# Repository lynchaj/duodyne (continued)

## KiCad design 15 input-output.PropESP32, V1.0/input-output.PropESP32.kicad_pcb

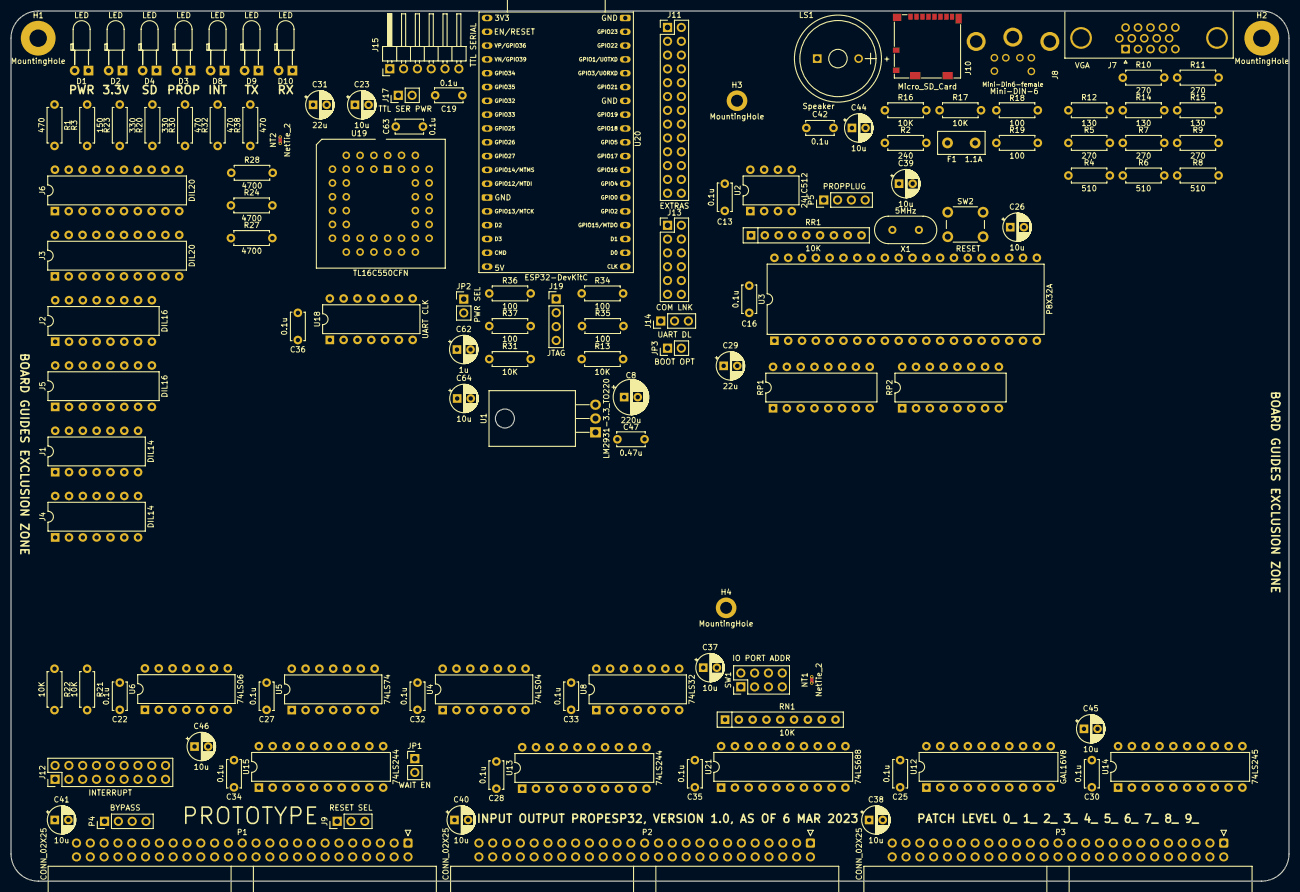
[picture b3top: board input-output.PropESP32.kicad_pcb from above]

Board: 2 copper layers, 235.0 x 160.0 mm, 127 parts (0 on the bottom side), 192 nets, no tracks yet.

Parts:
C8: 220u; CP_Radial_D6.3mm_P2.50mm
C13, C16, C19, C22, C25, C27, C28, C30, C32, C33, C34, C35, C36, C42, C63: 0.1u; C_Disc_D5.0mm_W2.5mm_P5.00mm
C23, C26, C37, C38, C39, C40, C41, C44, C45, C46, C64: 10u; CP_Radial_D5.0mm_P2.50mm
C29, C31: 22u; CP_Radial_D5.0mm_P2.50mm
C47: 0.47u; C_Disc_D5.0mm_W2.5mm_P5.00mm
C62: 1u; CP_Radial_D5.0mm_P2.50mm
D1, D2, D3, D4, D8, D9, D10: LED; LED_D3.0mm_Horizontal_O3.81mm_Z2.0mm
F1: 1.1A; Fuse_Littelfuse_395Series
H1, H2: MountingHole; MountingHole_3.2mm_M3_Pad
H3, H4: MountingHole; MountingHole_2.2mm_M2_DIN965_Pad
J1, J4: DIL14; DIP-14_W7.62mm
J2, J5: DIL16; DIP-16_W7.62mm
J3, J6: DIL20; DIP-20_W7.62mm
J7: VGA; DSUB-15-HD_Female_Horizontal_P2.29x1.98mm_EdgePinOffset3.03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
J8: Mini-DIN-6; mini-din6-female
J9: RESET SEL; PinHeader_1x03_P2.54mm_Vertical
J10: Micro_SD_Card; microSD_HC_Molex_104031-0811
J11: EXTRAS; PinHeader_2x13_P2.54mm_Vertical
J12: INTERRUPT; PinHeader_2x09_P2.54mm_Vertical
J13: COM LNK; PinHeader_2x06_P2.54mm_Vertical
J14: UART DL; PinHeader_1x03_P2.54mm_Vertical
J15: TTL SERIAL; PinHeader_1x06_P2.54mm_Horizontal
J17: TTL SER PWR; PinHeader_1x02_P2.54mm_Vertical
J19: JTAG; PinHeader_1x04_P2.54mm_Vertical
JP1: WAIT EN; PinHeader_1x02_P2.54mm_Vertical
JP2: PWR SEL; PinHeader_1x02_P2.54mm_Vertical
JP3: BOOT OPT; PinHeader_1x02_P2.54mm_Vertical
LS1: Speaker; MagneticBuzzer_StarMicronics_HMB-06_HMB-12
NT1, NT2: NetTie_2; NetTie-2_THT_Pad0.3mm
P1, P2, P3: CONN_02X25; IDC-Header_2x25_P2.54mm_Horizontal
P4: BYPASS; PinHeader_1x04_P2.54mm_Vertical
P5: PROPPLUG; PinHeader_1x04_P2.54mm_Vertical
R1, R30, R32, R38: 470; R_Axial_DIN0207_L6.3mm_D2.5mm_P7.62mm_Horizontal
R2: 240; R_Axial_DIN0207_L6.3mm_D2.5mm_P7.62mm_Horizontal
R3: 150; R_Axial_DIN0207_L6.3mm_D2.5mm_P7.62mm_Horizontal
R4, R6, R8: 510; R_Axial_DIN0207_L6.3mm_D2.5mm_P7.62mm_Horizontal
R5, R7, R9, R10, R11: 270; R_Axial_DIN0207_L6.3mm_D2.5mm_P7.62mm_Horizontal
R12, R14, R15: 130; R_Axial_DIN0207_L6.3mm_D2.5mm_P7.62mm_Horizontal
R13, R16, R17, R21, R22, R31: 10K; R_Axial_DIN0207_L6.3mm_D2.5mm_P7.62mm_Horizontal
R18, R19, R34, R35, R36, R37: 100; R_Axial_DIN0207_L6.3mm_D2.5mm_P7.62mm_Horizontal
R20, R23: 330; R_Axial_DIN0207_L6.3mm_D2.5mm_P7.62mm_Horizontal
R24, R27, R28: 4700; R_Axial_DIN0207_L6.3mm_D2.5mm_P7.62mm_Horizontal
RN1: 10K; R_Array_SIP9
RP1, RP2: 4700; DIP-16_W7.62mm
RR1: 10K; R_Array_SIP9
SW1: IO PORT ADDR; PinHeader_2x04_P2.54mm_Vertical
SW2: RESET; SW_PUSH_6mm
U1: LM2931-3.3_TO220; TO-220-3_Horizontal_TabDown
U2: 24LC512; DIP-8_W7.62mm
U3: P8X32A; DIP-40_W15.24mm
U4: 74LS04; DIP-14_W7.62mm
U5: 74LS74; DIP-14_W7.62mm
U6: 74LS06; DIP-14_W7.62mm
U8: 74LS32; DIP-14_W7.62mm
U12: GAL16V8; DIP-20_W7.62mm
U13, U15: 74LS244; DIP-20_W7.62mm
U14: 74LS245; DIP-20_W7.62mm
U18: UART CLK; DIP-14_W7.62mm
U19: TL16C550CFN; PLCC-44_THT-Socket
U20: ESP32-DevKitC
U21: 74LS688; DIP-20_W7.62mm
X1: 5MHz; Crystal_HC49-4H_Vertical

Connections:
+12V: P2.19, P2.20
-12V: P2.37, P2.38
/ESP32/CLK-ESP32: J11.22, U20.20 (SD_CLK/GPIO6)
/ESP32/CLK_UART: U18.8, U18.11, U19.18 (XIN)
/ESP32/CMD: J11.24, U20.18 (CMD)
/ESP32/EN: C62.1, R31.1, U20.2 (CHIP_PU)
/ESP32/INT: U6.9, U6.11, U19.33 (INTR)
/ESP32/IO0: JP3.1 (A), U20.25 (*GPIO0/BOOT/ADC2_CH1)
/ESP32/IO2: J11.16, U20.24 (ADC2_CH2/*GPIO2)
/ESP32/IO4: J13.2, U20.26 (ADC2_CH0/GPIO4)
/ESP32/IO5: J13.4, U20.29 (*GPIO5)
/ESP32/IO16: J11.14, U20.27 (GPIO16)
/ESP32/IO17: J11.12, U20.28 (GPIO17)
/ESP32/IO18: J13.6, U20.30 (GPIO18)
/ESP32/IO19: J13.8, U20.31 (GPIO19)
/ESP32/IO21: J11.8, U20.33 (GPIO21)
/ESP32/IO22: J11.6, U20.36 (GPIO22)
/ESP32/IO23: J11.4, U20.37 (GPIO23)
/ESP32/IO25: J11.15, U20.9 (DAC_1/ADC2_CH8/GPIO25)
/ESP32/IO26: J11.17, U20.10 (DAC_2/ADC2_CH9/GPIO26)
/ESP32/IO27: J11.19, U20.11 (ADC2_CH7/GPIO27)
/ESP32/IO32: J11.11, U20.7 (32K_XP/GPIO32/ADC1_CH4)
/ESP32/IO33: J11.13, U20.8 (32K_XN/GPIO33/ADC1_CH5)
/ESP32/IO34: J11.7, U20.5 (VDET_1/GPIO34/ADC1_CH6)
/ESP32/IO35: J11.9, U20.6 (VDET_2/GPIO35/ADC1_CH7)
/ESP32/MTCK: R37.1, U20.15 (MTCK/GPIO13/ADC2_CH4)
/ESP32/MTDI: R34.1, U20.13 (*MTDI/GPIO12/ADC2_CH5)
/ESP32/MTDO: R35.1, U20.23 (*MTDO/GPIO15/ADC2_CH3)
/ESP32/MTMS: R36.1, U20.12 (MTMS/GPIO14/ADC2_CH6)
/ESP32/RXD: J13.12, J14.2, U20.34 (U0RXD/GPIO3)
/ESP32/SD0: J11.20, U20.21 (SD_DATA0/GPIO7)
/ESP32/SD1: J11.18, U20.22 (SD_DATA1/GPIO8)
/ESP32/SD2: J11.23, U20.16 (SD_DATA2/GPIO9)
/ESP32/SD3: J11.25, U20.17 (SD_DATA3/GPIO10)
/ESP32/SENSOR_VN: J11.5, U20.4 (SENSOR_VN/GPIO39/ADC1_CH3)
/ESP32/SENSOR_VP: J11.3, U20.3 (SENSOR_VP/GPIO36/ADC1_CH0)
/ESP32/TTL_CTS#: J13.5, J15.6, U19.40 (~CTS)
/ESP32/TTL_RTS#: J13.7, J15.2, U19.36 (~RTS)
/ESP32/TTL_RX: J13.1, J13.9, J15.4, U8.12, U8.13, U19.11 (SIN)
/ESP32/TTL_TX: J13.3, J13.11, J15.5, U8.9, U8.10, U19.13 (SOUT)
/ESP32/TXD: J13.10, J14.3, U20.35 (U0TXD/GPIO1)
/ESP32/VCC_ESP32: JP2.2 (B), U20.19 (5V)
/ESP32/bRESET: R28.1, U4.8
/ESP32/pRESET: R28.2, U19.39 (MR)
/Propeller/BLUE: J7.3, R8.2, R9.2, R15.2
/Propeller/CLR: R13.2, U3.17 (P12), U4.3
/Propeller/DAT2: J10.1 (DAT2), R17.2
/Propeller/DI/CMD: J10.3 (CMD), RR1.5 (R4), U3.35 (P26)
/Propeller/DO/DAT0: J10.7 (DAT0), RR1.7 (R6), U3.33 (P24)
/Propeller/GREEN: J7.2, R6.2, R7.2, R14.2
/Propeller/HSYNC: J7.13, R10.2
/Propeller/KBD_CLK: R19.1, RR1.9 (R8), U3.20 (P15)
/Propeller/KBD_DAT: R18.1, RR1.8 (R7), U3.19 (P14)
/Propeller/KBD_VCC: F1.2, J7.9, J8.4
/Propeller/RED: J7.1, R4.2, R5.2, R12.2
/Propeller/RX: P5.3, U3.40 (P31)
/Propeller/SCL: RR1.3 (R2), U2.6 (SCL), U3.37 (P28)
/Propeller/SDA: RR1.2 (R1), U2.5 (SDA), U3.38 (P29)
/Propeller/SDCLK: J10.5 (CLK), RR1.6 (R5), U3.34 (P25)
/Propeller/SPK: R2.2, U3.18 (P13)
/Propeller/TX: P5.4, U3.39 (P30)
/Propeller/VSYNC: J7.14, R11.2
/Propeller/nIRQ/DAT1: J10.8 (DAT1), R16.2
/Propeller/~nCS/DAT3: J10.2 (DAT3/CD), RR1.4 (R3), U3.36 (P27), U6.3
A0: P2.35, U13.2 (I0a)
A1: P2.33, U13.4 (I1a)
A2: P2.31, U13.6 (I2a)
A3: P2.29, U13.8 (I3a)
A4: P2.27, U13.11 (I0b)
A5: P2.25, U13.13 (I1b)
A6: P2.23, U13.15 (I2b)
A7: P2.21, U13.17 (I3b)
D0: P3.33, U14.2 (I0a)
D1: P3.31, U14.4 (I1a)
D2: P3.29, U14.6 (I2a)
D3: P3.27, U14.8 (I3a)
D4: P3.25, U14.11 (I0b)
D5: P3.23, U14.13 (I1b)
D6: P3.21, U14.15 (I2b)
D7: P3.19, U14.17 (I3b)
GND: C8.2, C13.2, C16.2, C19.2, C22.2, C23.2, C25.2, C26.2, C27.2, C28.2, C29.2, C30.2, C31.2, C32.2, C33.2, C34.2, C35.2, C36.2, C37.2, C38.2, C39.2, C40.2, C41.2, C42.2, C45.2, C46.2, C47.2, C62.2, C63.2, C64.2, D1.1 (K), D2.1 (K), H1.1, H2.1, J7.0, J7.5, J7.6, J7.7, J7.8, J7.10, J8.3, J10.6 (VSS), J10.9 (SHIELD), J11.2, J11.10, J11.21, J14.1, J15.1, JP3.2 (B), LS1.1, NT1.1, P1.49, P1.50, P2.49, P2.50, P3.49, P3.50, P5.1, R12.1, R14.1, R15.1, SW2.1, U1.2 (GND), U2.1 (A0), U2.2 (A1), U2.3 (A2), U2.4 (GND), U2.7 (WP), U3.9 (VSS), U3.10 (BOEn), U3.29 (VSS), U4.7 (GND), U5.7 (GND), U6.7 (GND), U8.7 (GND), U12.10 (GND), U13.10 (GND), U14.10 (GND), U15.10 (GND), U18.4, U18.7, U19.22 (GND), U20.14 (GND), U20.32 (GND), U20.38 (GND), U21.10 (GND)
unnamed: C42.1, C44.1, R2.1
unnamed: C44.2, LS1.2
unnamed: D1.2 (A), R1.1
unnamed: D2.2 (A), R3.2
unnamed: D3.1 (K), R20.2
unnamed: D4.1 (K), U6.6
unnamed: D4.2 (A), R23.2
unnamed: D8.1 (K), U6.10
unnamed: D8.2 (A), R30.2
unnamed: D9.1 (K), U8.8
unnamed: D9.2 (A), R32.2
unnamed: D10.1 (K), U8.11
unnamed: D10.2 (A), R38.2
unnamed: J8.1, R18.2
unnamed: J8.5, R19.2
unnamed: J9.2, U15.2 (I0a)
unnamed: J12.1, J12.3, J12.5, J12.7, J12.9, J12.11, J12.13, J12.15, J12.17, U6.8
unnamed: J15.3, J17.2
unnamed: J19.1, R36.2
unnamed: J19.2, R34.2
unnamed: J19.3, R37.2
unnamed: J19.4, R35.2
unnamed: JP1.1 (A), R21.2, U6.2
unnamed: R4.1, U3.28 (P23)
unnamed: R5.1, U3.27 (P22)
unnamed: R6.1, U3.26 (P21)
unnamed: R7.1, U3.25 (P20)
unnamed: R8.1, U3.24 (P19)
unnamed: R9.1, U3.23 (P18)
unnamed: R10.1, U3.22 (P17)
unnamed: R11.1, U3.21 (P16)
unnamed: R20.1, U5.6 (~Q)
unnamed: R22.2, U6.4, U6.5
unnamed: R24.2, U19.14 (CS0), U19.15 (CS1)
unnamed: R27.2, U19.21 (WR), U19.25 (RD), U19.28 (~ADS)
unnamed: RN1.2 (R1), SW1.1, U21.18 (R7)
unnamed: RN1.3 (R2), SW1.3, U21.16 (R6)
unnamed: RN1.4 (R3), SW1.5, U21.14 (R5)
unnamed: RN1.5 (R4), SW1.7, U21.12 (R4)
unnamed: RN1.9 (R8), U21.3 (R0), U21.4 (P1), U21.5 (R1), U21.6 (P2), U21.7 (R2), U21.8 (P3), U21.9 (R3)
unnamed: U3.30 (X1), X1.1
unnamed: U3.31 (X0), X1.2
unnamed: U4.2, U5.3 (C)
unnamed: U4.4, U5.1 (~R)
unnamed: U4.6, U8.2
unnamed: U5.5 (Q), U6.1
unnamed: U19.10 (RCLK), U19.17 (~BAUDOUT)
ONE: NT2.2, R24.1
VCC: C22.1, C25.1, C27.1, C28.1, C29.1, C30.1, C31.1, C32.1, C33.1, C34.1, C35.1, C37.1, C38.1, C39.1, C40.1, C41.1, C45.1, C46.1, C47.1, D3.2 (A), F1.1, J11.26, J17.1, JP2.1 (A), NT2.1, P1.1, P1.2, P2.1, P2.2, P3.1, P3.2, R1.2, R21.1, R22.1, R23.1, R30.1, R32.1, R38.1, RN1.1 (common), U1.1 (VI), U4.14 (VCC), U5.2 (D), U5.4 (~S), U5.14 (VCC), U6.14 (VCC), U8.14 (VCC), U12.20 (VCC), U13.20 (VCC), U14.20 (VCC), U15.20 (VCC), U21.20 (VCC)
VDD: C8.1, C13.1, C16.1, C19.1, C23.1, C26.1, C36.1, C63.1, C64.1, J10.4 (VDD), J11.1, R3.1, R13.1, R16.1, R17.1, R31.2, RR1.1 (common), U1.3 (VO), U2.8 (VCC), U3.12 (VDD), U3.32 (VDD), U18.1, U18.14, U19.44 (VCC), U20.1 (3V3)
ZERO: NT1.2, R27.1, SW1.2, SW1.4, SW1.6, SW1.8, U13.1 (OEa), U13.19 (OEb), U15.1 (OEa), U15.19 (OEb)
bA0: RP2.3 (R3.1), U13.18 (O0a)
bA1: RP2.4 (R4.1), U13.16 (O1a)
bA2: RP2.5 (R5.1), U13.14 (O2a)
bA3: U4.5, U8.4, U13.12 (O3a)
bA4: U13.9 (O0b), U21.11 (P4)
bA5: U13.7 (O1b), U21.13 (P5)
bA6: U13.5 (O2b), U21.15 (P6)
bA7: U13.3 (O3b), U21.17 (P7)
bD0: RP1.1 (R1.1), U14.18 (O0a)
bD1: RP1.2 (R2.1), U14.16 (O1a)
bD2: RP1.3 (R3.1), U14.14 (O2a)
bD3: RP1.4 (R4.1), U14.12 (O3a)
bD4: RP1.5 (R5.1), U14.9 (O0b)
bD5: RP1.6 (R6.1), U14.7 (O1b)
bD6: RP1.7 (R7.1), U14.5 (O2b)
bD7: RP1.8 (R8.1), U14.3 (O3b)
pA0: RP2.14 (R3.2), U3.14 (P9), U19.31 (A0)
pA1: RP2.13 (R4.2), U3.15 (P10), U19.30 (A1)
pA2: RP2.12 (R5.2), U19.29 (A2)
pD0: RP1.16 (R1.2), U3.1 (P0), U19.2 (D0)
pD1: RP1.15 (R2.2), U3.2 (P1), U19.3 (D1)
pD2: RP1.14 (R3.2), U3.3 (P2), U19.4 (D2)
pD3: RP1.13 (R4.2), U3.4 (P3), U19.5 (D3)
pD4: RP1.12 (R5.2), U3.5 (P4), U19.6 (D4)
pD5: RP1.11 (R6.2), U3.6 (P5), U19.7 (D5)
pD6: RP1.10 (R7.2), U3.7 (P6), U19.8 (D6)
pD7: RP1.9 (R8.2), U3.8 (P7), U19.9 (D7)
~BAI: P1.40, P4.4
~BAO: P1.42, P4.3
~CS_BRD: U8.1, U8.5, U14.19 (OEb), U21.19 (P=R)
~CS_PROP: RP2.1 (R1.1), U4.1, U8.3
~CS_SERIAL: RP2.2 (R2.1), U8.6
~EIRQ0: J12.4, P1.45
~EIRQ1: J12.6, P1.43
~EIRQ2: J12.8, P1.41
~EIRQ3: J12.10, P1.39
~EIRQ4: J12.12, P1.37
~EIRQ5: J12.14, P1.35
~EIRQ6: J12.16, P1.33
~EIRQ7: J12.18, P1.31
~IEI: P1.44, P4.2
~IEO: P1.46, P4.1
~INT0: J12.2, P1.17
~IORQ: P1.7, U15.11 (I0b)
~M1: P1.11, U15.13 (I1b)
~RD: P1.3, U14.1 (OEa), U15.17 (I3b)
~RES_IN: J9.1, P1.20
~RES_OUT: J9.3, P1.21
~WAIT: JP1.2 (B), P1.25
~WR: P1.5, U15.15 (I2b)
~bIORQ: U15.9 (O0b), U21.1 (G)
~bM1: U15.7 (O1b), U21.2 (P0)
~bRD: RP2.6 (R6.1), U15.3 (O3b)
~bRESET: RP2.8 (R8.1), U4.9, U15.18 (O0a)
~bWR: RP2.7 (R7.1), U15.5 (O2b)
~pCS_PROP: RP2.16 (R1.2), U3.13 (P8)
~pCS_SERIAL: RP2.15 (R2.2), U19.16 (~CS2)
~pRD: RP2.11 (R6.2), U3.16 (P11), U19.24 (~RD)
~pRESET: P5.2, RP2.9 (R8.2), SW2.2, U3.11 (RESn)
~pWR: RP2.10 (R7.2), U19.20 (~WR)

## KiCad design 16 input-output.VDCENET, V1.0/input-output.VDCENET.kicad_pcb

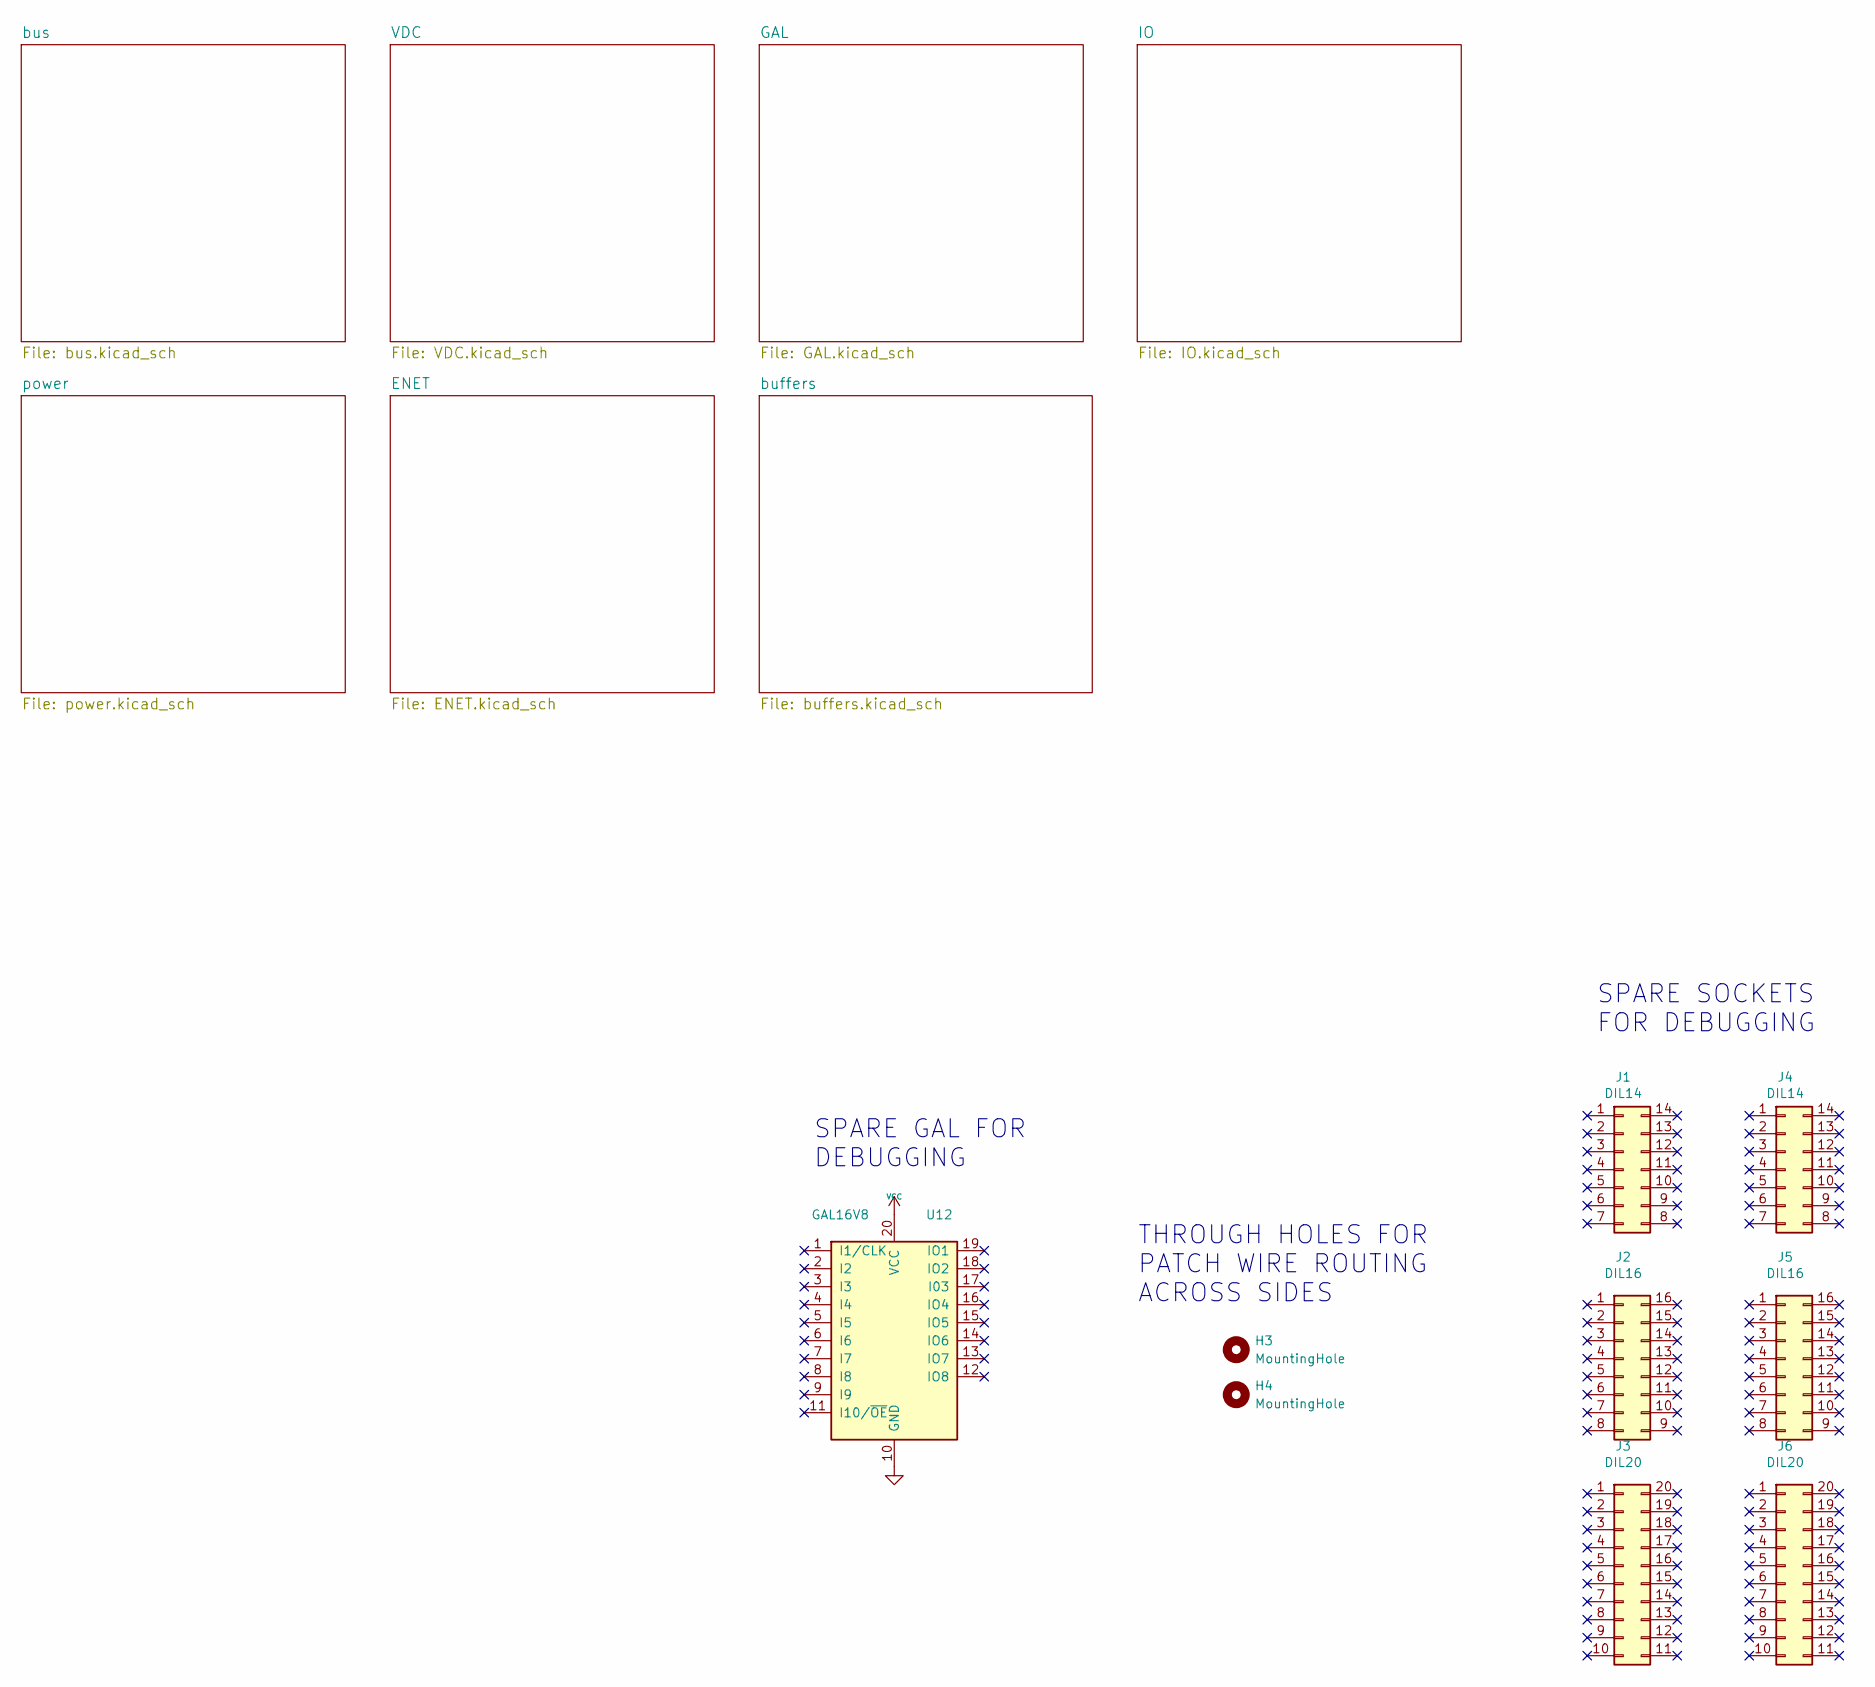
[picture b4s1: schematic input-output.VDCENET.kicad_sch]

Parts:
H3, H4: MountingHole; MountingHole_2.2mm_M2_DIN965_Pad
J1, J4: DIL14; DIP-14_W7.62mm
J2, J5: DIL16; DIP-16_W7.62mm
J3, J6: DIL20; DIP-20_W7.62mm
U12: GAL16V8; DIP-20_W7.62mm

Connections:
GND: U12.10 (GND); also elsewhere on the board
VCC: U12.20 (VCC); also elsewhere on the board

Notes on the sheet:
SPARE SOCKETS FOR DEBUGGING
SPARE GAL FOR DEBUGGING
THROUGH HOLES FOR PATCH WIRE ROUTING ACROSS SIDES

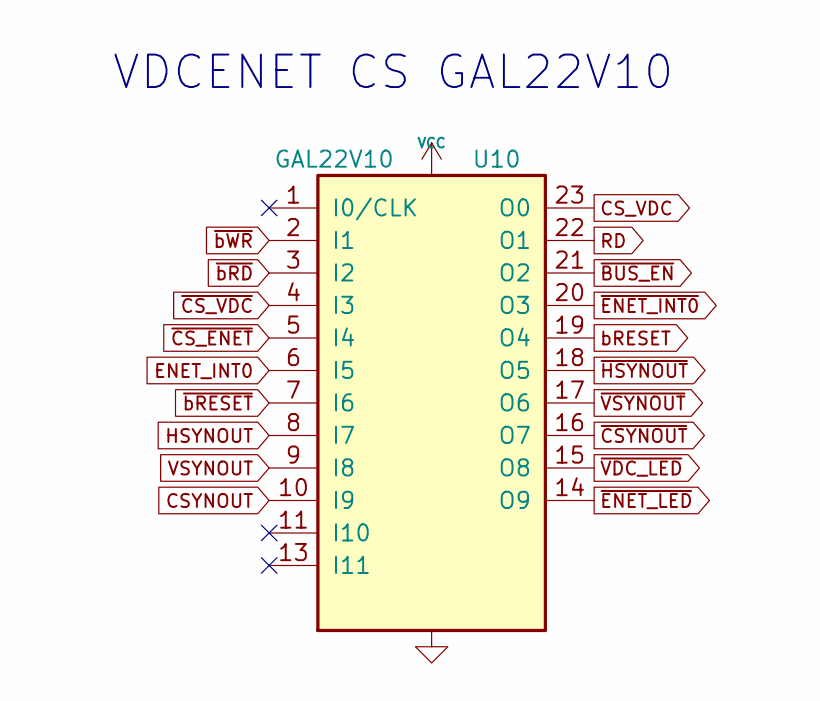
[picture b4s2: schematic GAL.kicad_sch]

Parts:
U10: GAL22V10; DIP-24_W7.62mm_Socket

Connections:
CSYNOUT: U10.10 (I9); also elsewhere on the board
CS_VDC: U10.23 (O0); also elsewhere on the board
ENET_INT0: U10.6 (I5); also elsewhere on the board
GND: U10.12 (GND); also elsewhere on the board
HSYNOUT: U10.8 (I7); also elsewhere on the board
RD: U10.22 (O1); also elsewhere on the board
VCC: U10.24 (VCC); also elsewhere on the board
VSYNOUT: U10.9 (I8); also elsewhere on the board
bRESET: U10.19 (O4); also elsewhere on the board
~BUS_EN: U10.21 (O2); also elsewhere on the board
~CSYNOUT: U10.16 (O7); also elsewhere on the board
~CS_ENET: U10.5 (I4); also elsewhere on the board
~CS_VDC: U10.4 (I3); also elsewhere on the board
~ENET_INT0: U10.20 (O3); also elsewhere on the board
~ENET_LED: U10.14 (O9); also elsewhere on the board
~HSYNOUT: U10.18 (O5); also elsewhere on the board
~VDC_LED: U10.15 (O8); also elsewhere on the board
~VSYNOUT: U10.17 (O6); also elsewhere on the board
~bRD: U10.3 (I2); also elsewhere on the board
~bRESET: U10.7 (I6); also elsewhere on the board
~bWR: U10.2 (I1); also elsewhere on the board

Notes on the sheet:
VDCENET CS GAL22V10

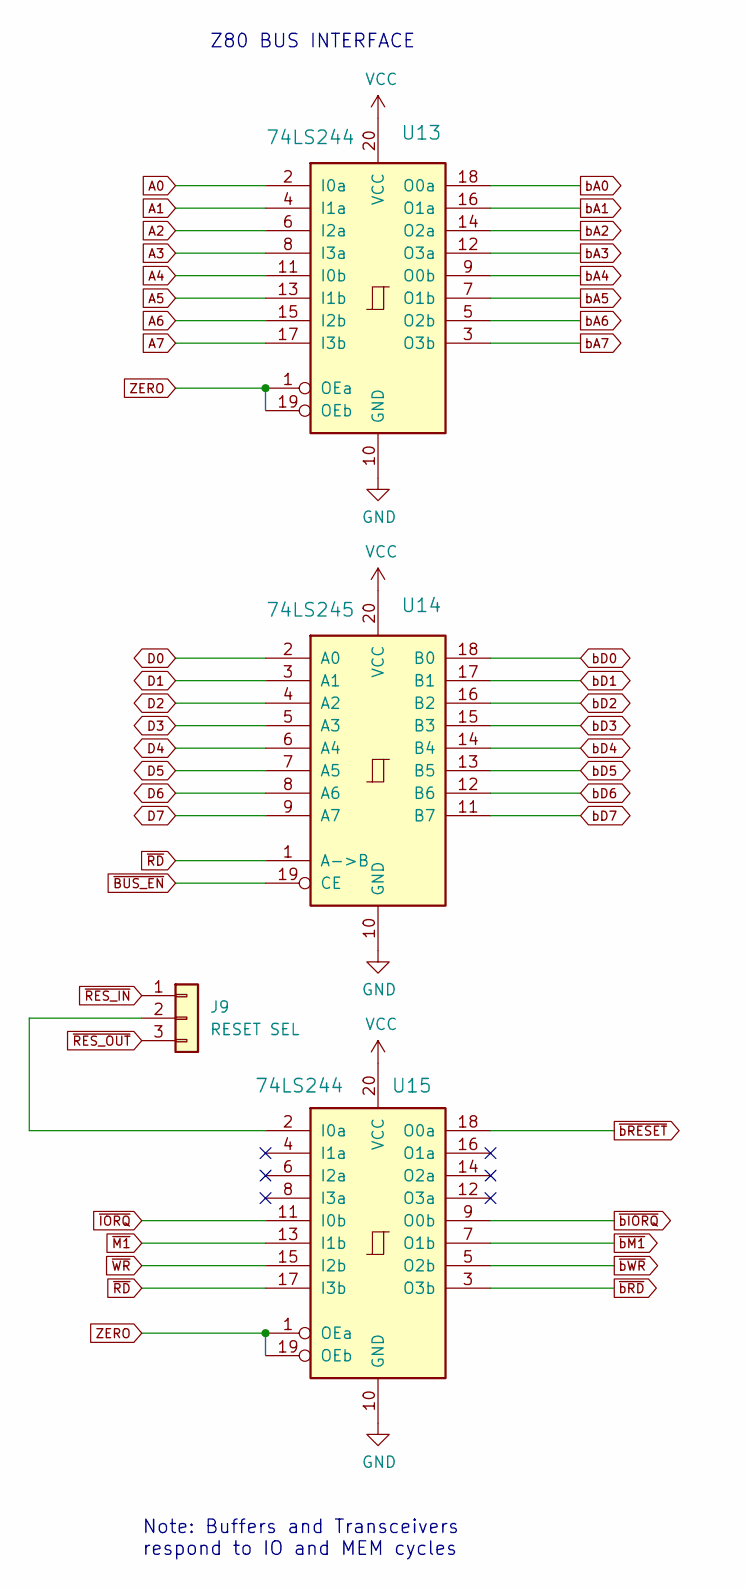
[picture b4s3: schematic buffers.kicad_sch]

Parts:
J9: RESET SEL; PinHeader_1x03_P2.54mm_Vertical
U13, U15: 74LS244; DIP-20_W7.62mm_Socket
U14: 74LS245; DIP-20_W7.62mm_Socket

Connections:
A0: U13.2 (I0a); also elsewhere on the board
A1: U13.4 (I1a); also elsewhere on the board
A2: U13.6 (I2a); also elsewhere on the board
A3: U13.8 (I3a); also elsewhere on the board
A4: U13.11 (I0b); also elsewhere on the board
A5: U13.13 (I1b); also elsewhere on the board
A6: U13.15 (I2b); also elsewhere on the board
A7: U13.17 (I3b); also elsewhere on the board
D0: U14.2 (A0); also elsewhere on the board
D1: U14.3 (A1); also elsewhere on the board
D2: U14.4 (A2); also elsewhere on the board
D3: U14.5 (A3); also elsewhere on the board
D4: U14.6 (A4); also elsewhere on the board
D5: U14.7 (A5); also elsewhere on the board
D6: U14.8 (A6); also elsewhere on the board
D7: U14.9 (A7); also elsewhere on the board
GND: U13.10 (GND), U14.10 (GND), U15.10 (GND); also elsewhere on the board
unnamed: J9.2, U15.2 (I0a)
VCC: U13.20 (VCC), U14.20 (VCC), U15.20 (VCC); also elsewhere on the board
ZERO: U13.1 (OEa), U13.19 (OEb), U15.1 (OEa), U15.19 (OEb); also elsewhere on the board
bA0: U13.18 (O0a); also elsewhere on the board
bA1: U13.16 (O1a); also elsewhere on the board
bA2: U13.14 (O2a); also elsewhere on the board
bA3: U13.12 (O3a); also elsewhere on the board
bA4: U13.9 (O0b); also elsewhere on the board
bA5: U13.7 (O1b); also elsewhere on the board
bA6: U13.5 (O2b); also elsewhere on the board
bA7: U13.3 (O3b); also elsewhere on the board
bD0: U14.18 (B0); also elsewhere on the board
bD1: U14.17 (B1); also elsewhere on the board
bD2: U14.16 (B2); also elsewhere on the board
bD3: U14.15 (B3); also elsewhere on the board
bD4: U14.14 (B4); also elsewhere on the board
bD5: U14.13 (B5); also elsewhere on the board
bD6: U14.12 (B6); also elsewhere on the board
bD7: U14.11 (B7); also elsewhere on the board
~BUS_EN: U14.19 (CE); also elsewhere on the board
~IORQ: U15.11 (I0b); also elsewhere on the board
~M1: U15.13 (I1b); also elsewhere on the board
~RD: U14.1 (A->B), U15.17 (I3b); also elsewhere on the board
~RES_IN: J9.1; also elsewhere on the board
~RES_OUT: J9.3; also elsewhere on the board
~WR: U15.15 (I2b); also elsewhere on the board
~bIORQ: U15.9 (O0b); also elsewhere on the board
~bM1: U15.7 (O1b); also elsewhere on the board
~bRD: U15.3 (O3b); also elsewhere on the board
~bRESET: U15.18 (O0a); also elsewhere on the board
~bWR: U15.5 (O2b); also elsewhere on the board

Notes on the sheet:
Z80 BUS INTERFACE
Note: Buffers and Transceivers respond to IO and MEM cycles

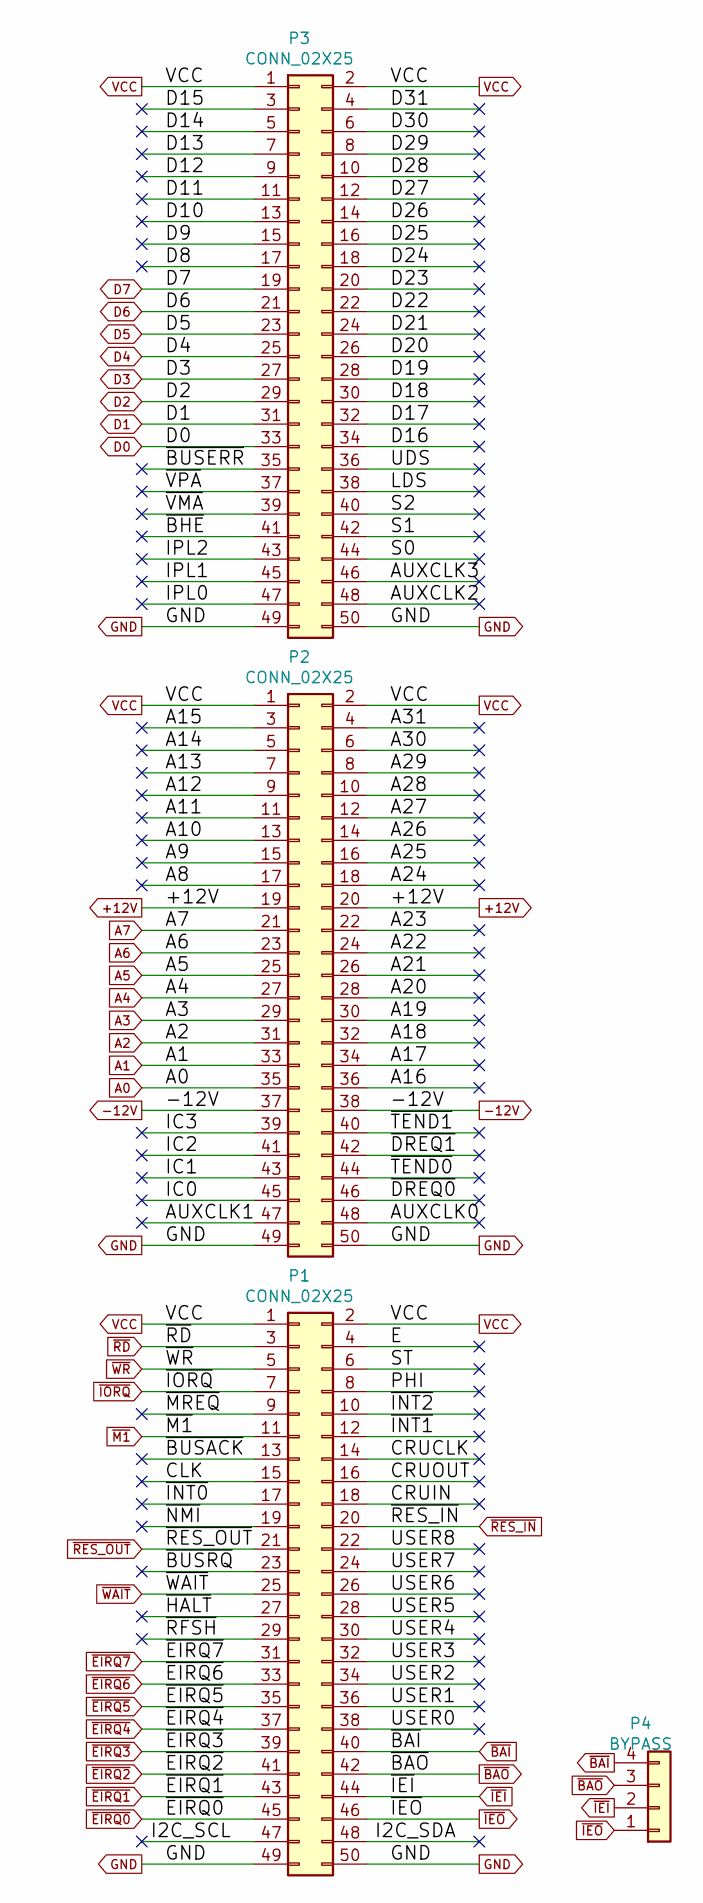
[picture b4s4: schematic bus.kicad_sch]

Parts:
P1, P2, P3: CONN_02X25; IDC-Header_2x25_P2.54mm_Horizontal
P4: BYPASS; PinHeader_1x04_P2.54mm_Vertical

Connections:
+12V: P2.19, P2.20
-12V: P2.37, P2.38
/bus/A8: P2.17
/bus/A9: P2.15
/bus/A10: P2.13
/bus/A11: P2.11
/bus/A12: P2.9
/bus/A13: P2.7
/bus/A14: P2.5
/bus/A15: P2.3
/bus/A16: P2.36
/bus/A17: P2.34
/bus/A18: P2.32
/bus/A19: P2.30
/bus/A20: P2.28
/bus/A21: P2.26
/bus/A22: P2.24
/bus/A23: P2.22
/bus/A24: P2.18
/bus/A25: P2.16
/bus/A26: P2.14
/bus/A27: P2.12
/bus/A28: P2.10
/bus/A29: P2.8
/bus/A30: P2.6
/bus/A31: P2.4
/bus/AUXCLK0: P2.48
/bus/AUXCLK1: P2.47
/bus/AUXCLK2: P3.48
/bus/AUXCLK3: P3.46
/bus/CLK: P1.15
/bus/CRUCLK: P1.14
/bus/CRUIN: P1.18
/bus/CRUOUT: P1.16
/bus/D8: P3.17
/bus/D9: P3.15
/bus/D10: P3.13
/bus/D11: P3.11
/bus/D12: P3.9
/bus/D13: P3.7
/bus/D14: P3.5
/bus/D15: P3.3
/bus/D16: P3.34
/bus/D17: P3.32
/bus/D18: P3.30
/bus/D19: P3.28
/bus/D20: P3.26
/bus/D21: P3.24
/bus/D22: P3.22
/bus/D23: P3.20
/bus/D24: P3.18
/bus/D25: P3.16
/bus/D26: P3.14
/bus/D27: P3.12
/bus/D28: P3.10
/bus/D29: P3.8
/bus/D30: P3.6
/bus/D31: P3.4
/bus/E: P1.4
/bus/I2C_SCL: P1.47
/bus/I2C_SDA: P1.48
/bus/IC0: P2.45
/bus/IC1: P2.43
/bus/IC2: P2.41
/bus/IC3: P2.39
/bus/IPL0: P3.47
/bus/IPL1: P3.45
/bus/IPL2: P3.43
/bus/LDS: P3.38
/bus/PHI: P1.8
/bus/S0: P3.44
/bus/S1: P3.42
/bus/S2: P3.40
/bus/ST: P1.6
/bus/UDS: P3.36
/bus/USER0: P1.38
/bus/USER1: P1.36
/bus/USER2: P1.34
/bus/USER3: P1.32
/bus/USER4: P1.30
/bus/USER5: P1.28
/bus/USER6: P1.26
/bus/USER7: P1.24
/bus/USER8: P1.22
/bus/~BHE: P3.41
/bus/~BUSACK: P1.13
/bus/~BUSERR: P3.35
/bus/~BUSRQ: P1.23
/bus/~DREQ0: P2.46
/bus/~DREQ1: P2.42
/bus/~HALT: P1.27
/bus/~INT0: P1.17
/bus/~INT1: P1.12
/bus/~INT2: P1.10
/bus/~MREQ: P1.9
/bus/~NMI: P1.19
/bus/~RFSH: P1.29
/bus/~TEND0: P2.44
/bus/~TEND1: P2.40
/bus/~VMA: P3.39
/bus/~VPA: P3.37
A0: P2.35; also elsewhere on the board
A1: P2.33; also elsewhere on the board
A2: P2.31; also elsewhere on the board
A3: P2.29; also elsewhere on the board
A4: P2.27; also elsewhere on the board
A5: P2.25; also elsewhere on the board
A6: P2.23; also elsewhere on the board
A7: P2.21; also elsewhere on the board
D0: P3.33; also elsewhere on the board
D1: P3.31; also elsewhere on the board
D2: P3.29; also elsewhere on the board
D3: P3.27; also elsewhere on the board
D4: P3.25; also elsewhere on the board
D5: P3.23; also elsewhere on the board
D6: P3.21; also elsewhere on the board
D7: P3.19; also elsewhere on the board
GND: P1.49, P1.50, P2.49, P2.50, P3.49, P3.50; also elsewhere on the board
VCC: P1.1, P1.2, P2.1, P2.2, P3.1, P3.2; also elsewhere on the board
~BAI: P1.40, P4.4
~BAO: P1.42, P4.3
~IEI: P1.44, P4.2
~IEO: P1.46, P4.1
~IORQ: P1.7; also elsewhere on the board
~M1: P1.11; also elsewhere on the board
~RD: P1.3; also elsewhere on the board
~RES_IN: P1.20; also elsewhere on the board
~RES_OUT: P1.21; also elsewhere on the board
~WAIT: P1.25; also elsewhere on the board
~WR: P1.5; also elsewhere on the board

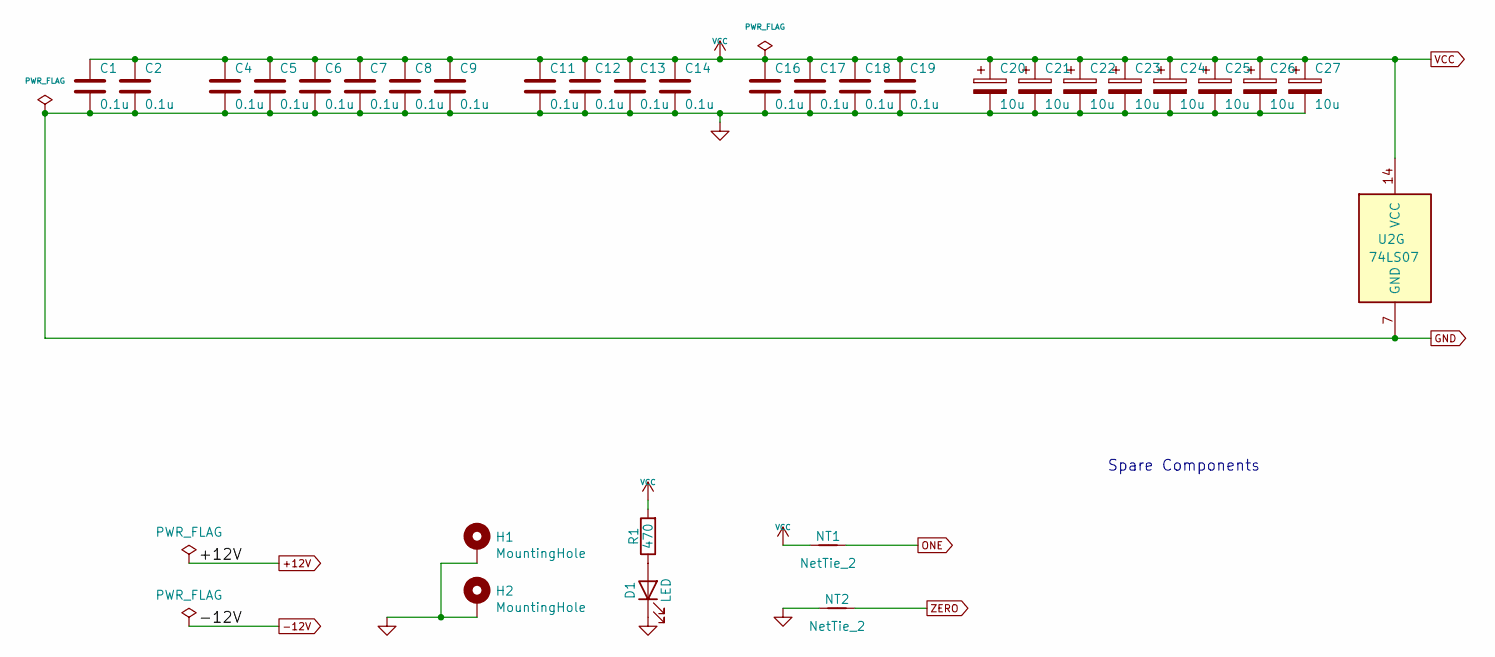
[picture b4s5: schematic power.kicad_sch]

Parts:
C1, C2, C4, C5, C6, C7, C8, C9, C11, C12, C13, C14, C16, C17, C18, C19: 0.1u; C_Disc_D5.0mm_W2.5mm_P5.00mm
C20, C21, C22, C23, C24, C25, C26, C27: 10u; CP_Radial_D5.0mm_P2.50mm
D1: LED; LED_D3.0mm_Horizontal_O3.81mm_Z2.0mm
H1, H2: MountingHole; MountingHole_3.2mm_M3_Pad
NT1, NT2: NetTie_2; NetTie-2_THT_Pad0.3mm
R1: 470; R_Axial_DIN0207_L6.3mm_D2.5mm_P7.62mm_Horizontal
U2: 74LS07; DIP-14_W7.62mm_Socket

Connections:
GND: C1.2, C2.2, C4.2, C5.2, C6.2, C7.2, C8.2, C9.2, C11.2, C12.2, C13.2, C14.2, C16.2, C17.2, C18.2, C19.2, C20.2, C21.2, C22.2, C23.2, C24.2, C25.2, C26.2, C27.2, D1.1 (K), H1.1, H2.1, NT2.1, U2.7 (GND); also elsewhere on the board
unnamed: D1.2 (A), R1.1
ONE: NT1.2; also elsewhere on the board
VCC: C1.1, C2.1, C4.1, C5.1, C6.1, C7.1, C8.1, C9.1, C11.1, C12.1, C13.1, C14.1, C16.1, C17.1, C18.1, C19.1, C20.1, C21.1, C22.1, C23.1, C24.1, C25.1, C26.1, C27.1, NT1.1, R1.2, U2.14 (VCC); also elsewhere on the board
ZERO: NT2.2; also elsewhere on the board

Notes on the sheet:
Spare Components
